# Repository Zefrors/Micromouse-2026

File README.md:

# Temple IEEE Micromouse 2026
Competing at IEEE SAC R1 & R2! https://attend.ieee.org/sac-2026/ on 3/20/26

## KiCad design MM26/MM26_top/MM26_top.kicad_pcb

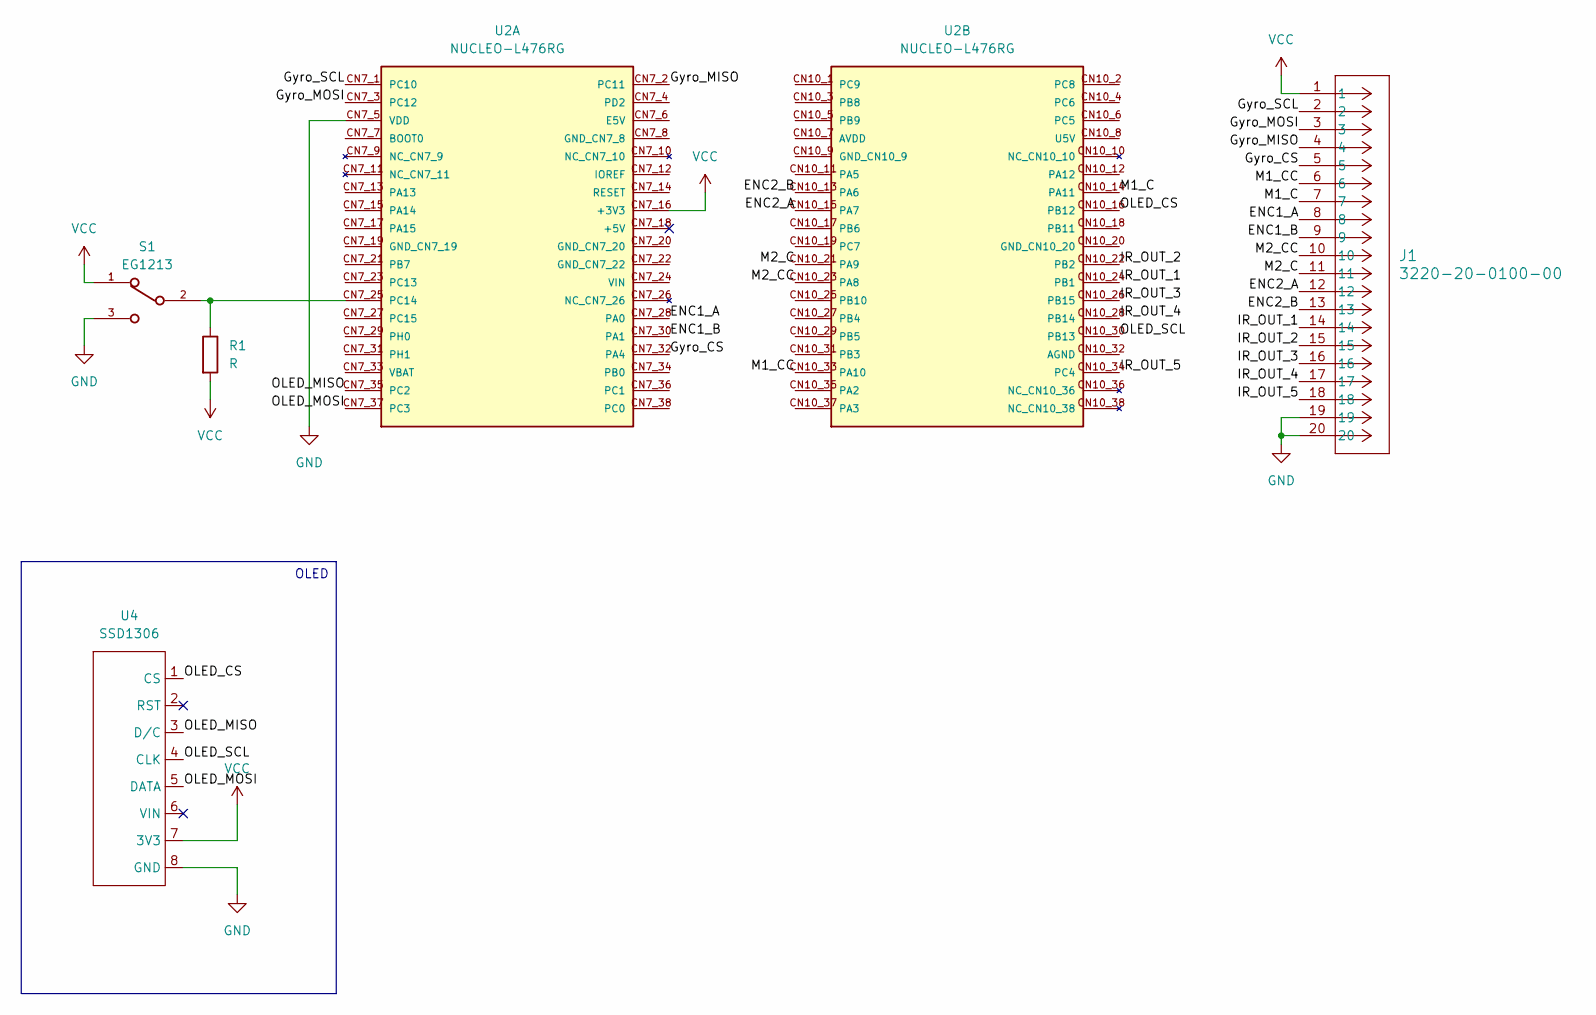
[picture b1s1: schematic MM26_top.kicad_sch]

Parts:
J1: 3220-20-0100-00; CONN20_3220-20_CNC
R1: R; R_0805_2012Metric_Pad1.20x1.40mm_HandSolder
S1: EG1213; SW_EG1213
U2: NUCLEO-L476RG; MODULE_NUCLEO-L476RG; PARTREV 15
U4: SSD1306

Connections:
/ENC1_A: J1.8, U2.CN7_28 (PA0)
/ENC1_B: J1.9, U2.CN7_30 (PA1)
/ENC2_A: J1.12, U2.CN10_15 (PA7)
/ENC2_B: J1.13, U2.CN10_13 (PA6)
/Gyro_CS: J1.5, U2.CN7_32 (PA4)
/Gyro_MISO: J1.4, U2.CN7_2 (PC11)
/Gyro_MOSI: J1.3, U2.CN7_3 (PC12)
/Gyro_SCL: J1.2, U2.CN7_1 (PC10)
/IR_OUT_1: J1.14, U2.CN10_24 (PB1)
/IR_OUT_2: J1.15, U2.CN10_22 (PB2)
/IR_OUT_3: J1.16, U2.CN10_26 (PB15)
/IR_OUT_4: J1.17, U2.CN10_28 (PB14)
/IR_OUT_5: J1.18, U2.CN10_34 (PC4)
/M1_C: J1.7, U2.CN10_14 (PA11)
/M1_CC: J1.6, U2.CN10_33 (PA10)
/M2_C: J1.11, U2.CN10_21 (PA9)
/M2_CC: J1.10, U2.CN10_23 (PA8)
/OLED_CS: U2.CN10_16 (PB12), U4.1 (CS)
/OLED_MISO: U2.CN7_35 (PC2), U4.3 (D/C)
/OLED_MOSI: U2.CN7_37 (PC3), U4.5 (DATA)
/OLED_SCL: U2.CN10_30 (PB13), U4.4 (CLK)
GND: J1.19, J1.20, S1.3, U2.CN7_5 (VDD), U4.8 (GND)
unnamed: R1.1, S1.2, U2.CN7_25 (PC14)
VCC: J1.1, R1.2, S1.1, U2.CN7_16 (+3V3), U4.7 (3V3)

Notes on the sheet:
OLED

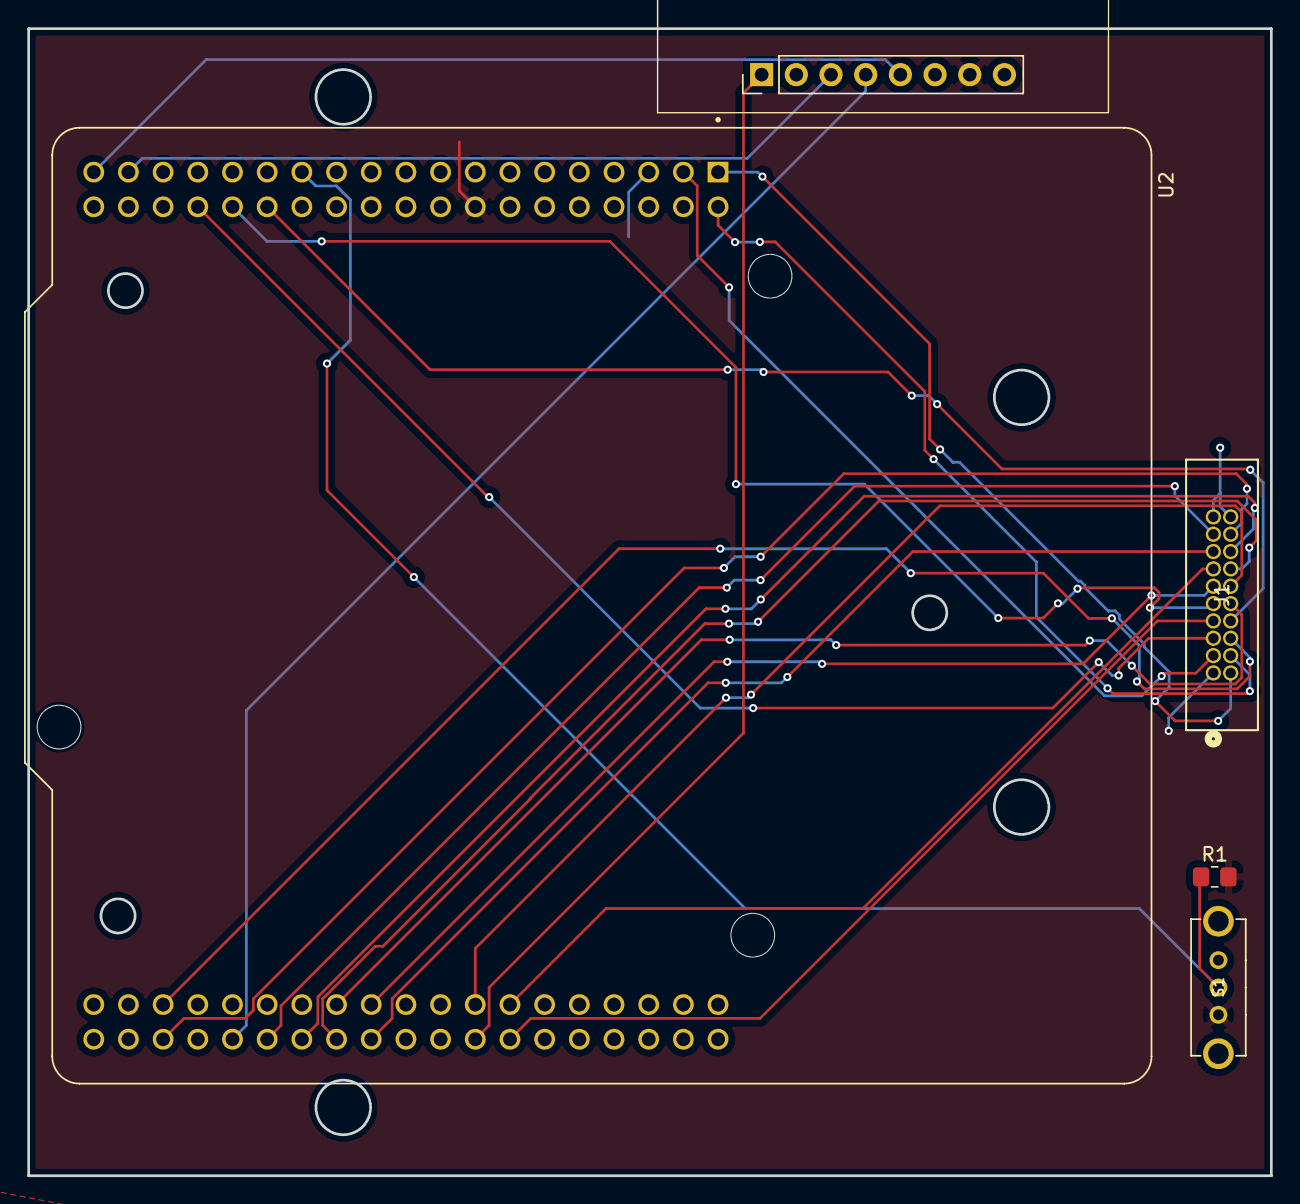
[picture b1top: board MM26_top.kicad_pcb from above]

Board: 2 copper layers, 91.0 x 84.0 mm, 5 parts (0 on the bottom side), 24 nets.

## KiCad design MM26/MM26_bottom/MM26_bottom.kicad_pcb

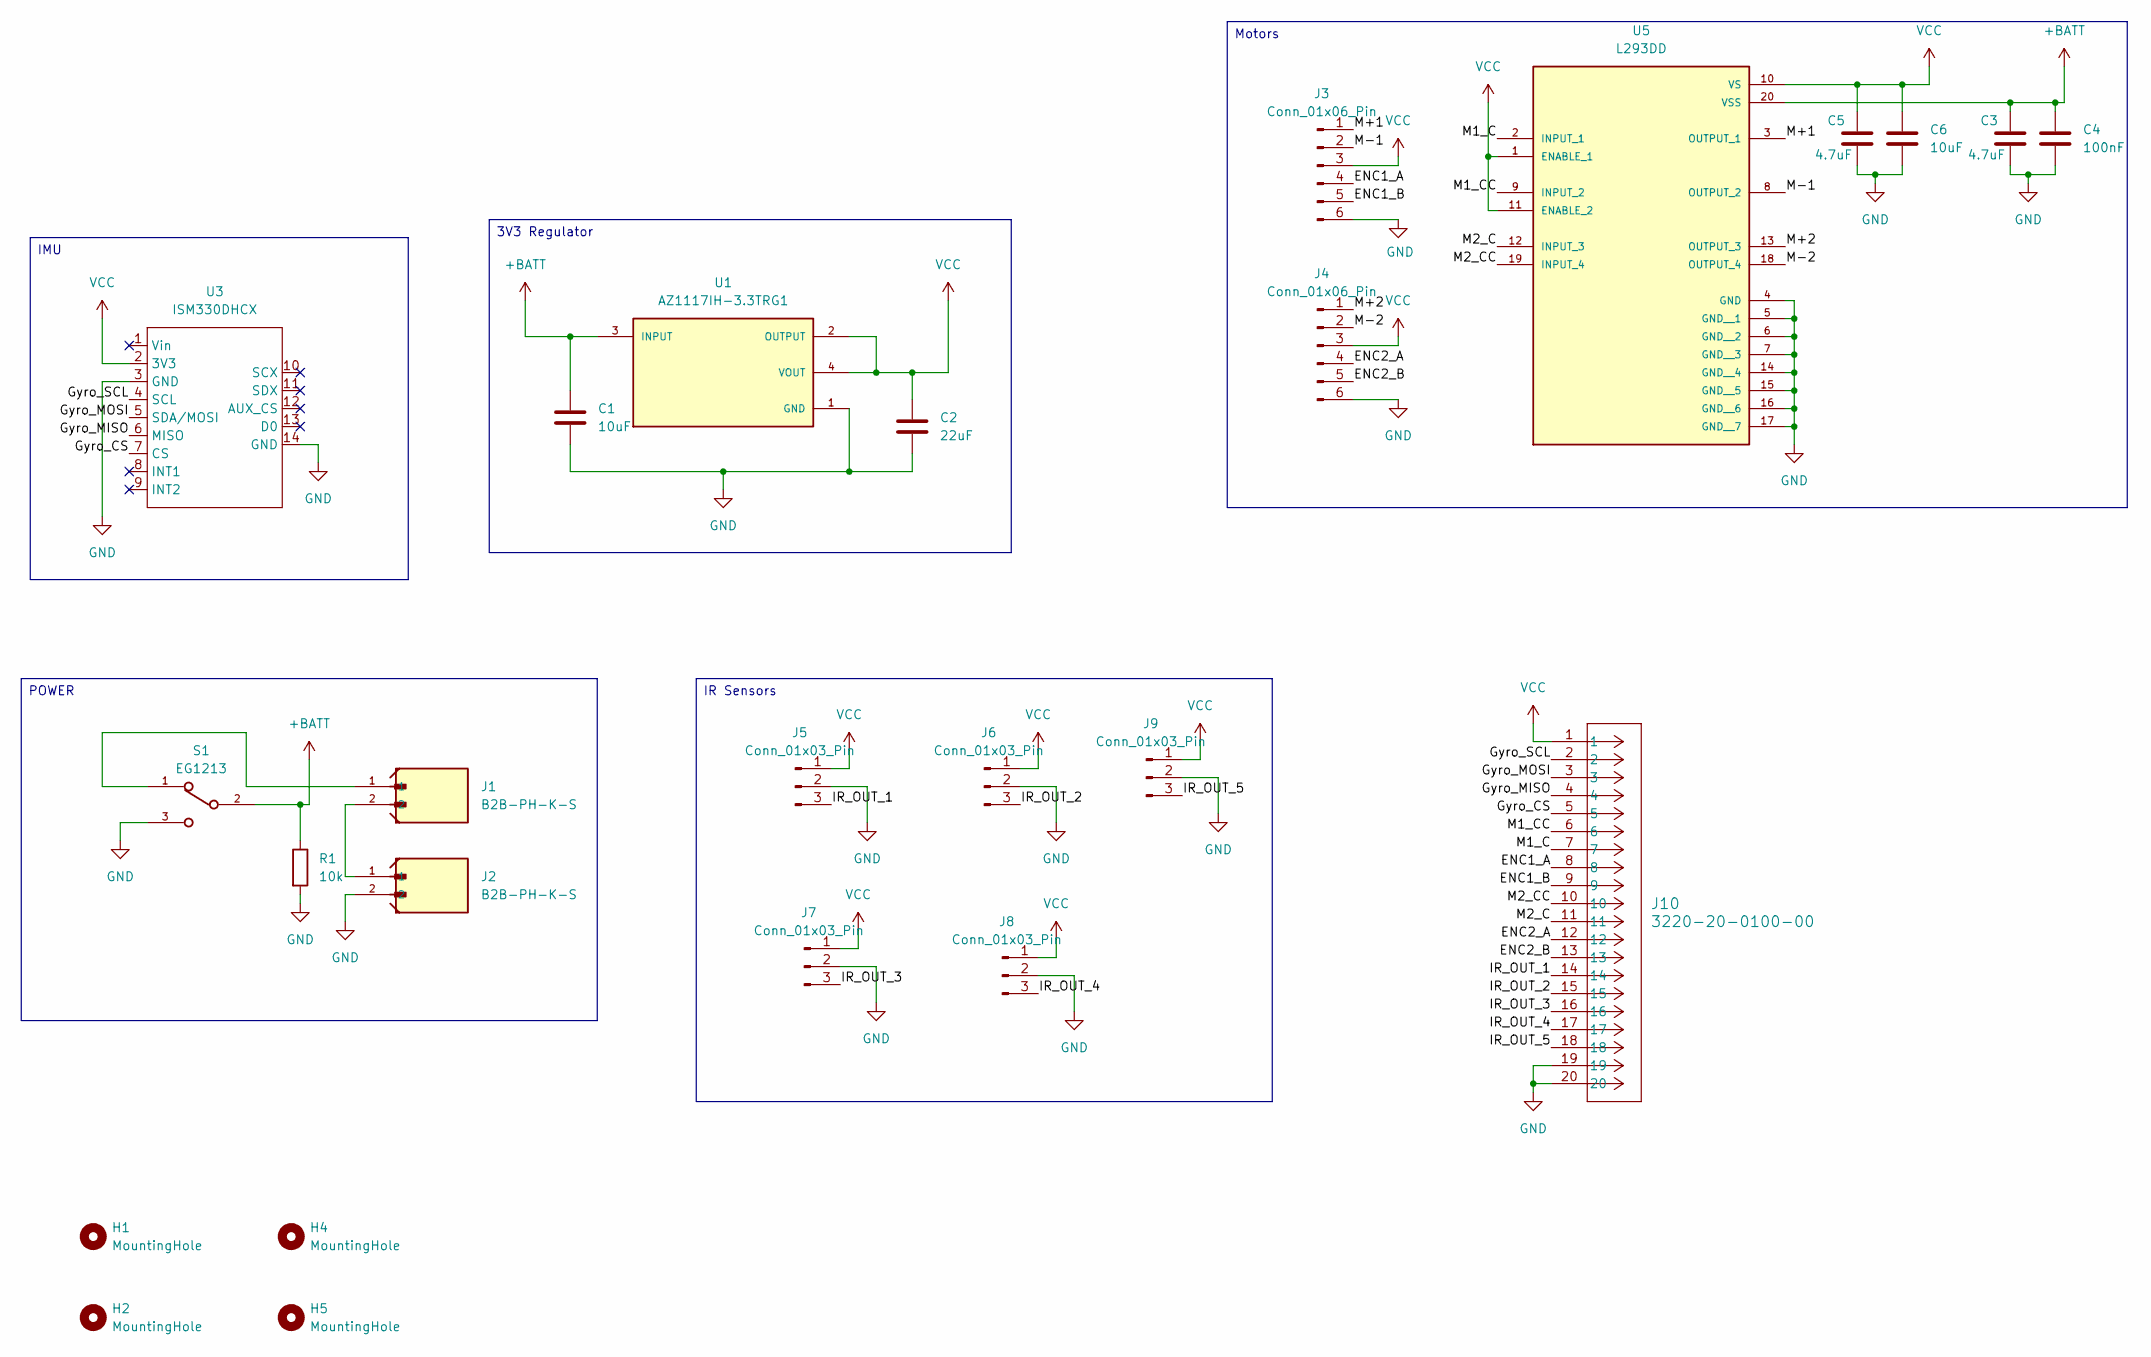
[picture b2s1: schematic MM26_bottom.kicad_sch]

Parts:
C1, C6: 10uF; C_0805_2012Metric_Pad1.18x1.45mm_HandSolder
C2: 22uF; C_0805_2012Metric_Pad1.18x1.45mm_HandSolder
C3, C5: 4.7uF; C_0805_2012Metric_Pad1.18x1.45mm_HandSolder
C4: 100nF; C_0805_2012Metric_Pad1.18x1.45mm_HandSolder
H1, H2, H4, H5: MountingHole; MountingHole_2.5mm
J1, J2: B2B-PH-K-S; JST_B2B-PH-K-S
J3, J4: Conn_01x06_Pin; JST_SH_BM06B-SRSS-TB_1x06-1MP_P1.00mm_Vertical
J5, J6, J7, J8, J9: Conn_01x03_Pin; PinSocket_1x03_P2.54mm_Horizontal
J10: 3220-20-0100-00; CONN20_3220-20_CNC
R1: 10k; R_0805_2012Metric_Pad1.20x1.40mm_HandSolder
S1: EG1213; SW_EG1213
U1: AZ1117IH-3.3TRG1; SOT230P700X185-4N; PARTREV 2-2
U3: ISM330DHCX
U5: L293DD; SOIC127P1032X265-20N; PARTREV N/A

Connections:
+BATT: C1.1, C3.1, C4.1, R1.1, S1.2, U1.3 (INPUT), U5.20 (VSS)
/ENC1_A: J3.4, J10.8
/ENC1_B: J3.5, J10.9
/ENC2_A: J4.4, J10.12
/ENC2_B: J4.5, J10.13
/Gyro_CS: J10.5, U3.7 (CS)
/Gyro_MISO: J10.4, U3.6 (MISO)
/Gyro_MOSI: J10.3, U3.5 (SDA/MOSI)
/Gyro_SCL: J10.2, U3.4 (SCL)
/IR_OUT_1: J5.3, J10.14
/IR_OUT_2: J6.3, J10.15
/IR_OUT_3: J7.3, J10.16
/IR_OUT_4: J8.3, J10.17
/IR_OUT_5: J9.3, J10.18
/M1_C: J10.7, U5.2 (INPUT_1)
/M1_CC: J10.6, U5.9 (INPUT_2)
/M2_C: J10.11, U5.12 (INPUT_3)
/M2_CC: J10.10, U5.19 (INPUT_4)
/M+1: J3.1, U5.3 (OUTPUT_1)
/M+2: J4.1, U5.13 (OUTPUT_3)
/M-1: J3.2, U5.8 (OUTPUT_2)
/M-2: J4.2, U5.18 (OUTPUT_4)
GND: C1.2, C2.2, C3.2, C4.2, C5.2, C6.2, J2.2, J3.6, J4.6, J5.2, J6.2, J7.2, J8.2, J9.2, J10.19, J10.20, R1.2, S1.3, U1.1 (GND), U3.3 (GND), U3.14 (GND), U5.4 (GND), U5.5 (GND__1), U5.6 (GND__2), U5.7 (GND__3), U5.14 (GND__4), U5.15 (GND__5), U5.16 (GND__6), U5.17 (GND__7)
unnamed: J1.1, S1.1
unnamed: J1.2, J2.1
VCC: C2.1, C5.1, C6.1, J3.3, J4.3, J5.1, J6.1, J7.1, J8.1, J9.1, J10.1, U1.2 (OUTPUT), U1.4 (VOUT), U3.2 (3V3), U5.1 (ENABLE_1), U5.10 (VS), U5.11 (ENABLE_2)

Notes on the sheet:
IMU
IR Sensors
Motors
POWER
3V3 Regulator

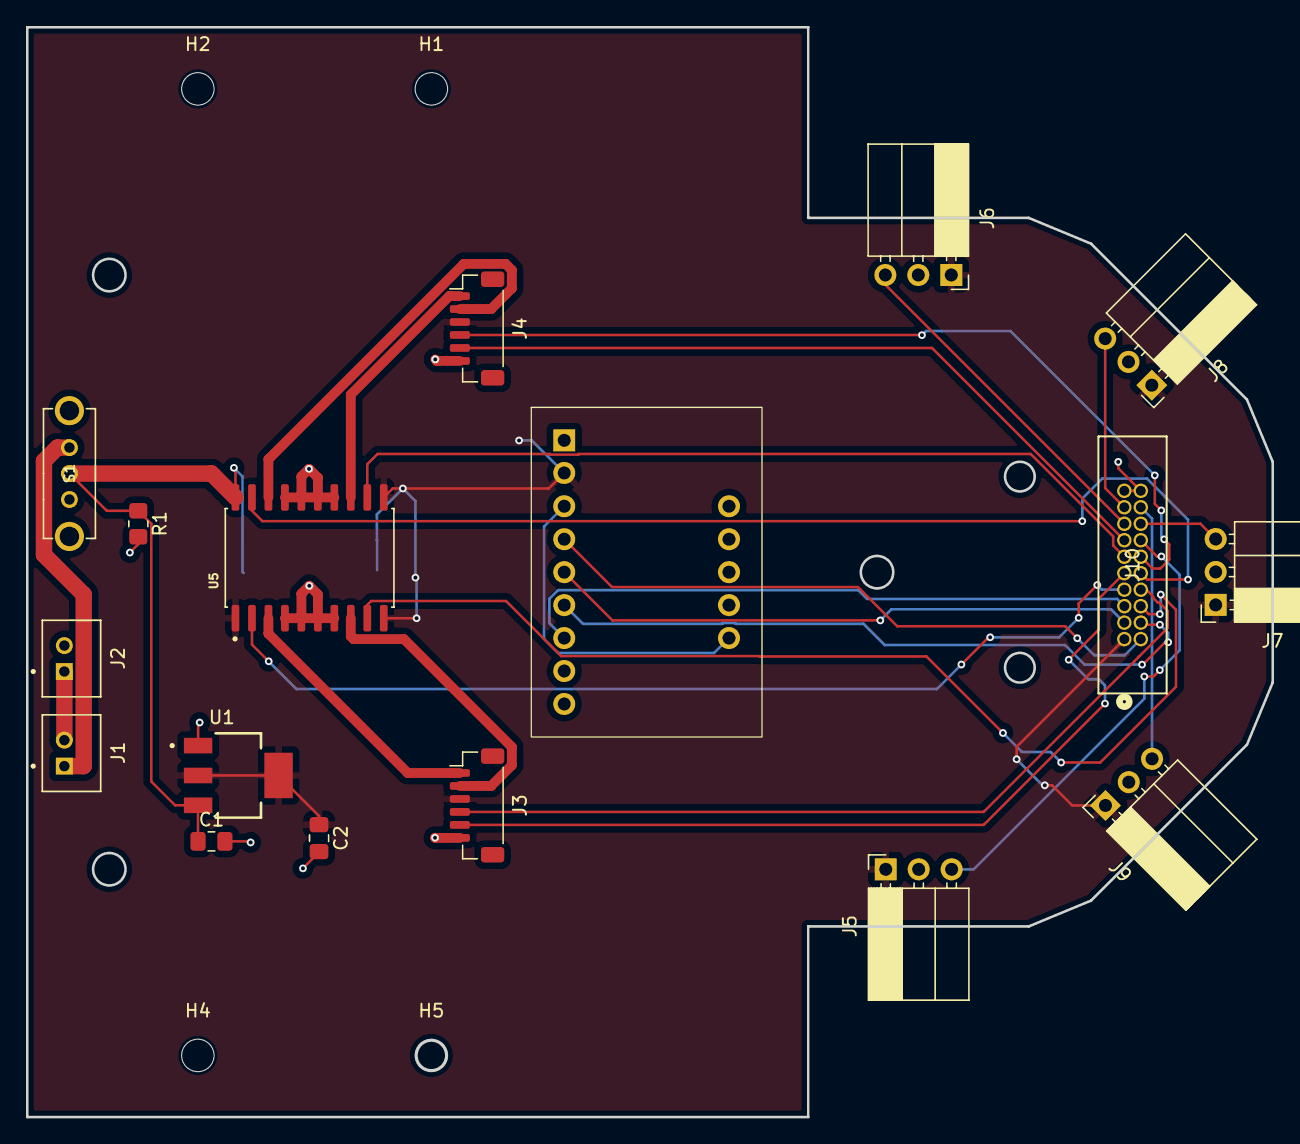
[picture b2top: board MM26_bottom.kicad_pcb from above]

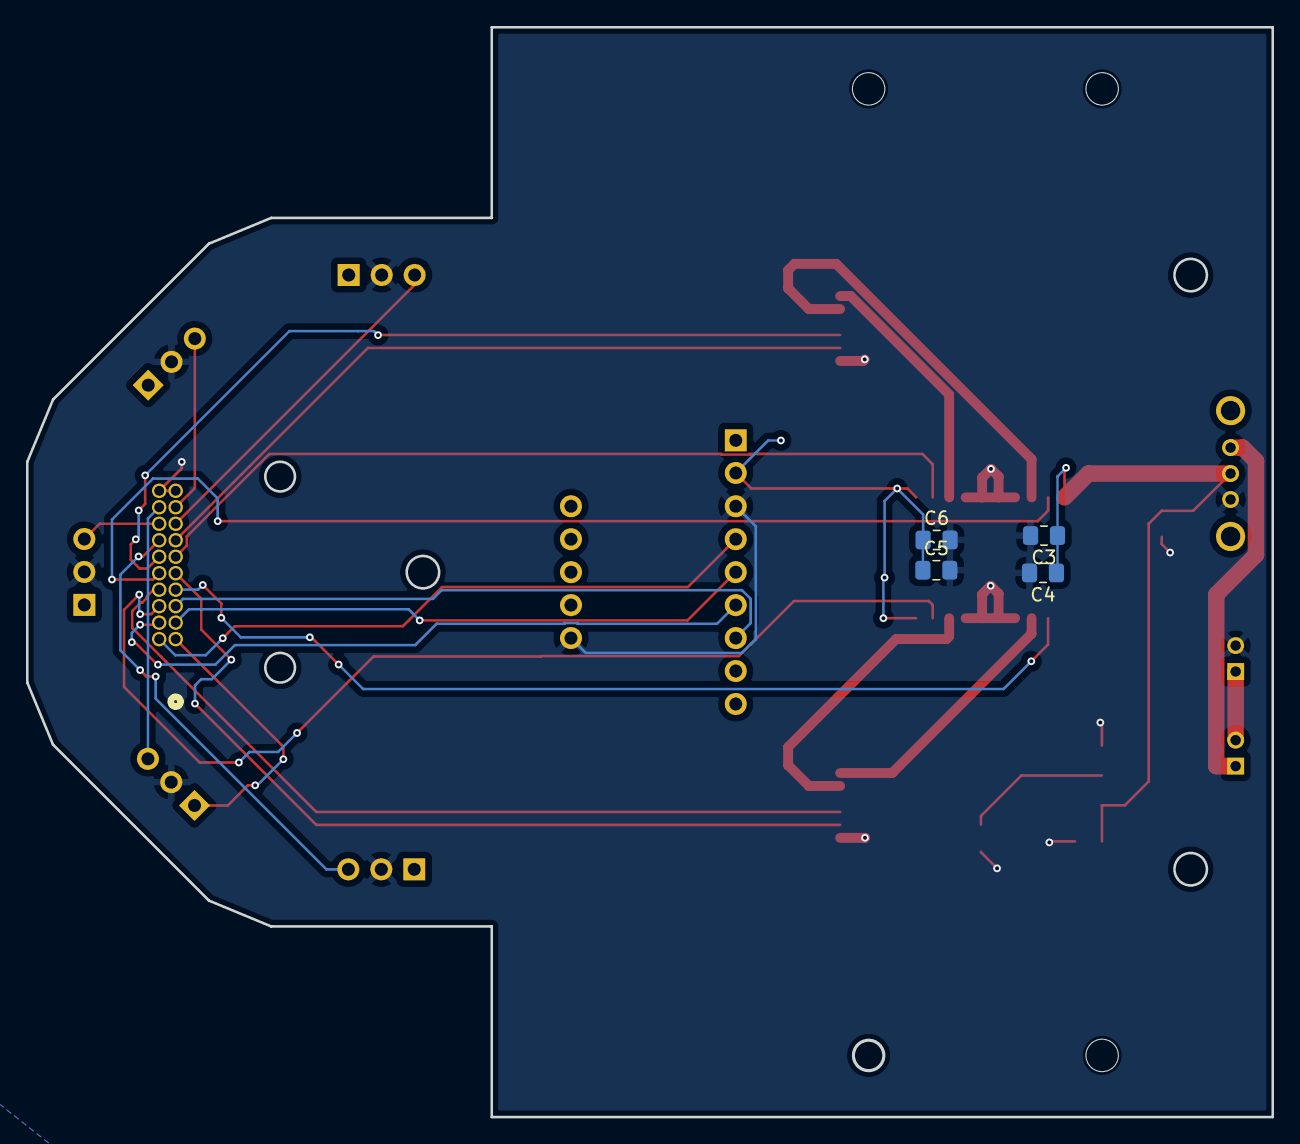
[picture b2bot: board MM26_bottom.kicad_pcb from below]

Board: 2 copper layers, 96.0 x 84.0 mm, 25 parts (4 on the bottom side), 26 nets.

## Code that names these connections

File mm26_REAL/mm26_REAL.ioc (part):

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Mcu.Name=STM32L476R(C-E-G)Tx
Mcu.Package=LQFP64
Mcu.UserName=STM32L476RGTx
PA0.GPIOParameters=GPIO_Label
PA0.GPIO_Label=ENC1_A
PA0.Signal=S_TIM2_CH1
PA1.GPIOParameters=GPIO_Label
PA1.GPIO_Label=ENC1_B
PA1.Signal=S_TIM2_CH2
PA10.GPIOParameters=GPIO_Label
PA10.GPIO_Label=M1_CC
PA10.Signal=S_TIM1_CH3
PA11.GPIOParameters=GPIO_Label
PA11.GPIO_Label=M1_C
PA11.Signal=S_TIM1_CH4
PA13\ (JTMS-SWDIO).GPIOParameters=GPIO_Label
PA13\ (JTMS-SWDIO).GPIO_Label=TMS
PA13\ (JTMS-SWDIO).Mode=Serial_Wire
PA13\ (JTMS-SWDIO).Signal=SYS_JTMS-SWDIO
PA14\ (JTCK-SWCLK).GPIOParameters=GPIO_Label
PA14\ (JTCK-SWCLK).GPIO_Label=TCK
PA14\ (JTCK-SWCLK).Mode=Serial_Wire
PA14\ (JTCK-SWCLK).Signal=SYS_JTCK-SWCLK
PA2.GPIOParameters=GPIO_Speed,GPIO_PuPd,GPIO_Label,GPIO_Mode
PA2.GPIO_Label=USART_TX
PA2.GPIO_Mode=GPIO_MODE_AF_PP
PA2.GPIO_PuPd=GPIO_NOPULL
PA2.GPIO_Speed=GPIO_SPEED_FREQ_VERY_HIGH
PA2.Mode=Asynchronous
PA2.Signal=USART2_TX
PA3.GPIOParameters=GPIO_Speed,GPIO_PuPd,GPIO_Label,GPIO_Mode
PA3.GPIO_Label=USART_RX
PA3.GPIO_Mode=GPIO_MODE_AF_PP
PA3.GPIO_PuPd=GPIO_NOPULL
PA3.GPIO_Speed=GPIO_SPEED_FREQ_VERY_HIGH
PA3.Mode=Asynchronous
PA3.Signal=USART2_RX
PA4.GPIOParameters=PinState,GPIO_Label
PA4.GPIO_Label=Gyro_CS
PA4.PinState=GPIO_PIN_SET
PA4.Signal=GPIO_Output
PA5.GPIOParameters=GPIO_Speed,GPIO_PuPd,GPIO_Label,GPIO_ModeDefaultOutputPP
PA5.GPIO_Label=LD2 [green Led]
PA5.GPIO_ModeDefaultOutputPP=GPIO_MODE_OUTPUT_PP
PA5.GPIO_PuPd=GPIO_NOPULL
PA5.GPIO_Speed=GPIO_SPEED_FREQ_LOW
PA5.Signal=GPIO_Output
PA6.GPIOParameters=GPIO_Label
PA6.GPIO_Label=ENC2_B
PA6.Signal=S_TIM3_CH1
PA7.GPIOParameters=GPIO_Label
PA7.GPIO_Label=ENC2_A
PA7.Signal=S_TIM3_CH2
PA8.GPIOParameters=GPIO_Label
PA8.GPIO_Label=M2_CC
PA8.Signal=S_TIM1_CH1
PA9.GPIOParameters=GPIO_Label
PA9.GPIO_Label=M2_C
PA9.Signal=S_TIM1_CH2
PB0.GPIOParameters=GPIO_Label
PB0.GPIO_Label=IR_IN_FRONT
PB0.Signal=ADCx_IN15
PB1.GPIOParameters=GPIO_Label
PB1.GPIO_Label=IR_IN_R
PB1.Signal=ADCx_IN16
PB12.GPIOParameters=GPIO_Label
PB12.GPIO_Label=OLED_CS
PB12.Signal=GPIO_Output
PB13.GPIOParameters=GPIO_Label
PB13.GPIO_Label=OLED_SCK
PB13.Mode=TX_Only_Simplex_Unidirect_Master
PB13.Signal=SPI2_SCK
PB3\ (JTDO-TRACESWO).GPIOParameters=GPIO_Label
PB3\ (JTDO-TRACESWO).GPIO_Label=SWO
PB3\ (JTDO-TRACESWO).Signal=SYS_JTDO-SWO
PC10.GPIOParameters=GPIO_Label
PC10.GPIO_Label=Gyro_SCK
PC10.Mode=Full_Duplex_Master
PC10.Signal=SPI3_SCK
PC11.GPIOParameters=GPIO_Label
PC11.GPIO_Label=Gyro_MISO
PC11.Mode=Full_Duplex_Master
PC11.Signal=SPI3_MISO
PC12.GPIOParameters=GPIO_Label
PC12.GPIO_Label=Gyro_MOSI
PC12.Mode=Full_Duplex_Master
PC12.Signal=SPI3_MOSI
PC13.GPIOParameters=GPIO_PuPd,GPIO_Label,GPIO_ModeDefaultEXTI
PC13.GPIO_Label=B1 [Blue PushButton]
PC13.GPIO_ModeDefaultEXTI=GPIO_MODE_IT_FALLING
PC13.GPIO_PuPd=GPIO_NOPULL
PC13.Signal=GPXTI13
PC14-OSC32_IN\ (PC14).Mode=LSE-External-Oscillator
PC14-OSC32_IN\ (PC14).Signal=RCC_OSC32_IN
PC15-OSC32_OUT\ (PC15).Mode=LSE-External-Oscillator
PC15-OSC32_OUT\ (PC15).Signal=RCC_OSC32_OUT
PC2.GPIOParameters=GPIO_Label
PC2.GPIO_Label=OLED_DC
PC2.Signal=GPIO_Output
PC3.GPIOParameters=GPIO_Label
PC3.GPIO_Label=OLED_MOSI
PC3.Mode=TX_Only_Simplex_Unidirect_Master
PC3.Signal=SPI2_MOSI
PC4.GPIOParameters=GPIO_Label
PC4.GPIO_Label=IR_IN_R_DIAG
PC4.Signal=ADCx_IN13
PC5.GPIOParameters=GPIO_Label
PC5.GPIO_Label=IR_IN_LEFT
PC5.Signal=ADCx_IN14
PC8.GPIOParameters=GPIO_Label
PC8.GPIO_Label=OLED_RST
PC8.Signal=GPIO_Output
PH0-OSC_IN\ (PH0).Mode=HSE-External-Oscillator
PH0-OSC_IN\ (PH0).Signal=RCC_OSC_IN
PH1-OSC_OUT\ (PH1).Mode=HSE-External-Oscillator
PH1-OSC_OUT\ (PH1).Signal=RCC_OSC_OUT
RCC.HSE_VALUE=8000000
RCC.SYSCLKFreq_VALUE=80000000
RCC.SYSCLKSource=RCC_SYSCLKSOURCE_PLLCLK
board=NUCLEO-L476RG
boardIOC=true

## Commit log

2026-01-29 created bill of parts
2026-01-29 Create Parts folder
2026-01-29 added kicad and voltage regulator
2026-01-30 added oled to bom
2026-01-30 imported MCU to KiCAD
2026-02-01 power
2026-02-03 Imported Everything
2026-02-03 H Bridge Wiring
2026-02-04 good enough schematic
2026-02-11 all components placed on pcb
    just need to route it now
2026-02-12 pcb done
2026-02-19 cut the thing in half
    forgot to upload this earlier
2026-03-10 STM32 FILES
    sorry for not pushing in eons
2026-03-10 motor code shell
2026-03-10 Set Motor Speed function Complete
2026-03-10 Encoder Method
2026-03-12 pictures
2026-03-12 PID Beginning
2026-03-12 Encoder reset added
2026-03-12 Reset Encoder updated
2026-03-13 Encoder Rest
2026-03-17 tryna gyro
2026-03-21 theoretical
    pid tuning yaaaay
2026-03-26 Competition Bot
    This is the state of the bot when we competed at rowan university 3/21/26. We placed 6th place out of 10.
